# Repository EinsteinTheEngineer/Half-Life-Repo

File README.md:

# Half-Life-Repo

# WEEK 1

PURPOSE:
The purpose of my project is to create a simple yet extremely useful Flight computer, that can also be used for rockets, and this would simply send data, of temperature, bearing, and height, I can also create a velocity time graph with velocity put on the graph, and then simple derivate that to get acceleration, or I can just use the accelerometer, the MPU, and use that to give me a A vs. T graph. Why it exists: The reason is that flight computer is expensive and this is a fully done PCB, instead of me having to use a breadboard and have to worry about a loose connection, I can asssure myself that the copper traces will work. I love building plane and rockets, but what I like more is seeing them work and not fail, for this I need data! So I created this board to collect me data and so if it does fail, why and how can I prevent it the next time.

My project is a flight computer that will have multiple sensors talk to and esp32 wroom chip that will write the data to an SD card that will store it. The board consists of the following: ESP32-WROOM chip, MPU6050, BMP280, and an SD card logger. This was my plan at first, and it was changed a lot though. I add a DC to DC Buck converter it would convert 6v dc to 3.3v dc for the esp to then spit out 3.3v logic.
Started as this:

Then added the extra components:

Wired ground and live:

Wired the MPU: 

Wired the BMP:

Wired the SD card:

Finalized Schematic:

After fighting the ERC test

Then routed the board:

The 3d View

And finally done!

Here is My BOM for the parts I am using:

Designator	Category	Part / Value	Qty	Package / Footprint	Est. Unit Price (USD)	Est. Line Total (USD)	Distributor Link
U1	IC / Module	Espressif ESP32-WROOM-32E (or 32U)	1	ESP32-WROOM-32	7.21	7.21	digikey.com
U2	Sensor	Bosch BMP280	1	LGA-8 (2.0x2.5mm)	3	3	digikey.com
U3	Sensor	TDK InvenSense MPU-6050	1	QFN-24 (4x4mm)	4.25	4.25	digikey.com
U4	Power IC	Diodes Inc. AP63203WU-7	1	TSOT-23-6	0.65	0.65	digikey.com
U5	Interface IC	WCH CH340C	1	SOP-16	0.9	0.9	lcsc.com
J1	Connector	MicroSD Card Slot (Push-Push)	1	MicroSD_Card_Det	1.1	1.1	digikey.com
J2	Connector	2-Pin JST-PH 2.0mm Header	1	JST_PH_B2B-PH-K	0.25	0.25	digikey.com
J3	Connector	HRO TYPE-C-31-M-12 (16-Pin USB-C)	1	USB_C_Receptacle_16P	0.55	0.55	lcsc.com
SW1	Switch	SPDT SMD Slide Switch	1	SW_SPDT_PCM12	0.4	0.4	digikey.com
Q1, Q2	Transistor	S8050 (or MMBT3904) NPN	2	SOT-23	0.1	0.2	digikey.com
D1, D2	Diode	B5819W Schottky Diode	2	SOD-123	0.15	0.3	digikey.com
R1, R2	Resistor	5.1 kΩ (1%)	2	0603 (1608 Metric)	0.1	0.2	digikey.com
R3, R4, R_EN, R_IO0, R_SD1–3	Resistor	10 kΩ (1%)	7	0603 (1608 Metric)	0.1	0.7	digikey.com
R_TX	Resistor	1 kΩ (1%)	1	0603 (1608 Metric)	0.1	0.1	digikey.com
R_SDA, R_SCL	Resistor	4.7 kΩ (1%)	2	0603 (1608 Metric)	0.1	0.2	digikey.com
C5	Capacitor	2.2 nF (50V X7R)	1	0603 (1608 Metric)	0.1	0.1	digikey.com
C1–C4, C_DEC1–5	Capacitor	100 nF (16V/25V X7R)	7	0603 (1608 Metric)	0.1	0.7	digikey.com
C_EN	Capacitor	1 µF (16V X7R)	1	0603 (1608 Metric)	0.1	0.1	digikey.com
C_IN, C_BULK1–2	Capacitor	10 µF (25V X5R/X7R)	3	0805 (2012 Metric)	0.15	0.45	digikey.com
C6	Capacitor	22 µF (16V X5R/X7R)	1	0805 (2012 Metric)	0.2	0.2	digikey.com
L1	Inductor	3.3 µH (≥1.5A Shielded)	1	1210 (3225 Metric)	0.45	0.45	digikey.com

# WEEK 2

The purpose of this project is the create an enclosure for my PCB that I designed in week 1, this will make sure it isn't just sitting in there just chilling, I made sure to add mounting holes, and vents to make sure it will sit there and that it will have some breathability, and so it can cool, with the use of a fan two, since it will also use its antenna to communicate with my computer that's on the ground. So that means I technically have two ways to get data, from the SD card and from communication with my computer. I would trust the SD card more since the computer may have lost packets on the way and it could not be as reliable as a SD card, but it there as another way to have data.

Me personally, I printed this with PLA, since its cheap, light weight, and it's not like there's going to be such high temperatures, hence there is also a fan there for a reason.
PLA, print with 10-15% infill, you'll probably need support material, I have a K1C so no multi-material, so I just printed PLA supports.

# WEEK 3

This week I decided to create a recorder, it records sounds and stuff like that. The purpose for why I wanted to do this was because it was relatively simple, plus I learned about this new board the ESP32-S3-Zero, it's so good. It so useful, though its small it does a lot of things whilst being small. I was the perfect addition to the board, and just the same simple way of coding it. At first, I was about to use the actual esp32, which was most definitely going to be overkill for this simple guy. This board is a breakout board kind of, since it doesn't have an on-board ESP but the board will be put onto the thing.

Fully routed Schematic

With the cut outs

3D view

Here's the BOM

"Reference","Qty","Value","DNP","Exclude from BOM","Exclude from Board","Footprint","Datasheet"
"C1","1","100","","","","Capacitor_SMD:C_0805_2012Metric","~"
"C2","1","10000","","","","Capacitor_SMD:C_0805_2012Metric","~"
"C3","1","C","","","","Capacitor_SMD:C_0805_2012Metric","~"
"D1","1","LED","","","","LED_THT:LED_D3.0mm","~"
"J1,J2","2","Conn_01x09_Pin","","","","Connector_PinSocket_2.54mm:PinSocket_1x09_P2.54mm_Vertical","~"
"J3","1","Conn_01x06_Pin","","","","Connector_PinSocket_2.54mm:PinSocket_1x06_P2.54mm_Vertical","~"
"J4","1","Micro_SD_Card","","","","Connector_Card:microSD_HC_Wuerth_693072010801","https://www.we-online.com/components/products/datasheet/693072010801.pdf"
"J5","1","Screw_Terminal_01x02","","","","TerminalBlock_Phoenix:TerminalBlock_Phoenix_MKDS-1,5-2-5.08_1x02_P5.08mm_Horizontal","~"
"R1","1","330","","","","Resistor_SMD:R_0805_2012Metric","~"
"SW1","1","SW_Push","","","","Button_Switch_THT:SW_PUSH_6mm","~"

# WEEK 4

This week I focused on a weather and display thing. This was a simple yet easy idea that I would like to keep on my desk. It will show date, time, weather, and just a sleek design. The purpose of this was to create something very useful, and it will be simple enough to be easy to do.

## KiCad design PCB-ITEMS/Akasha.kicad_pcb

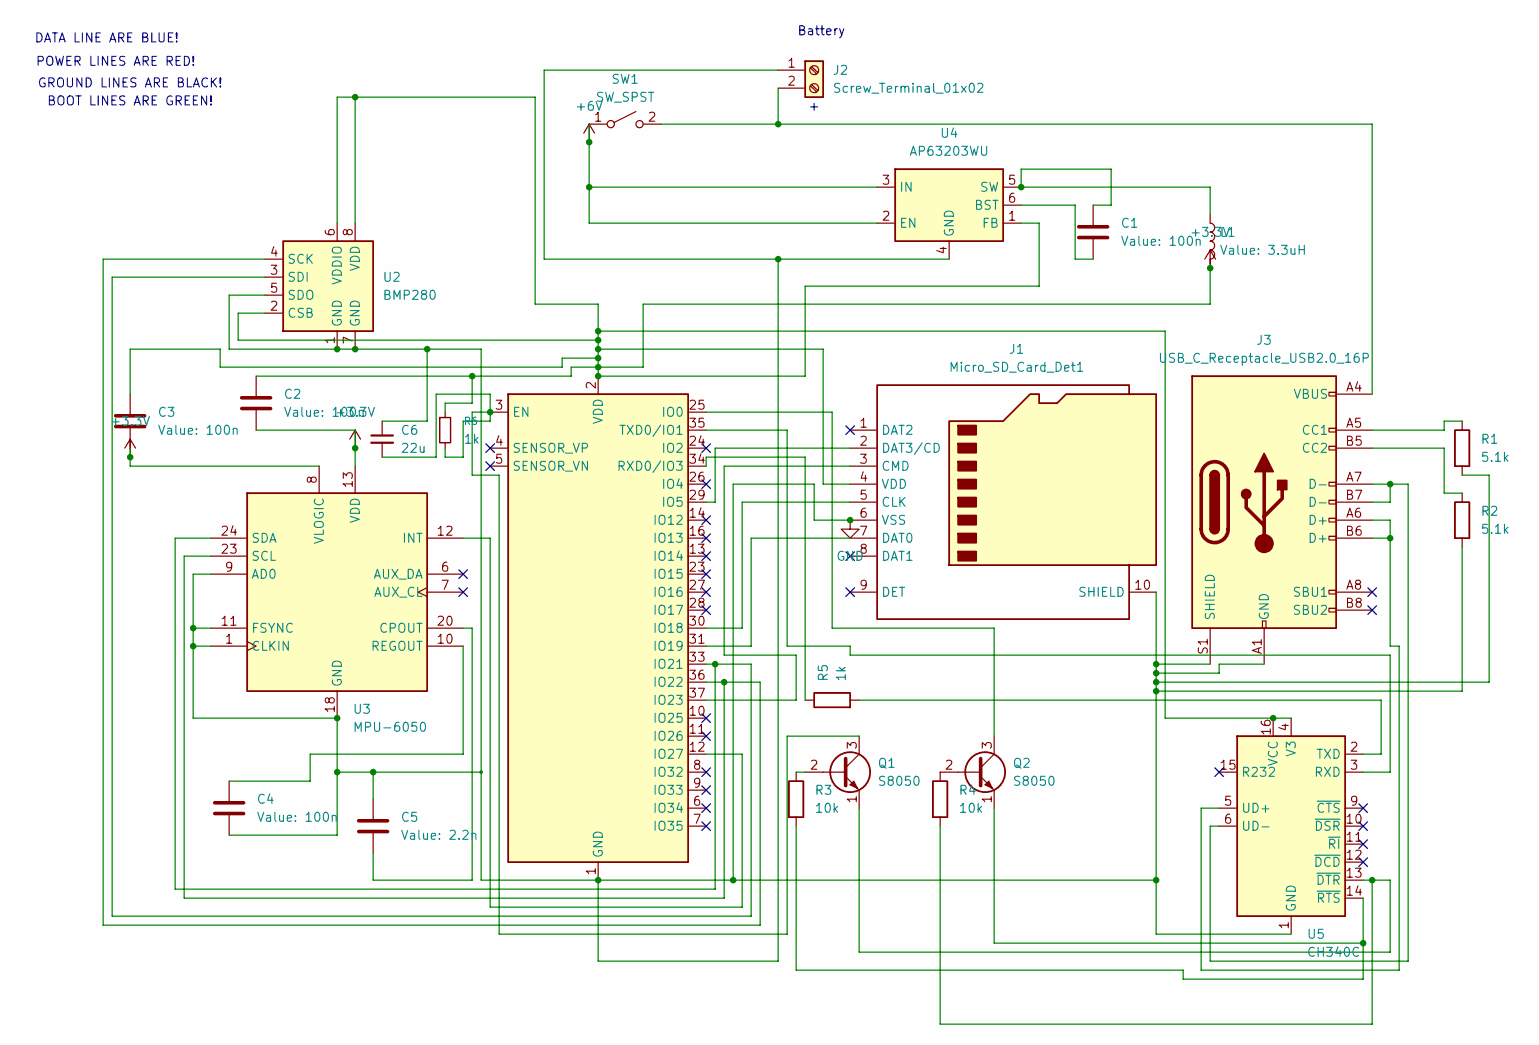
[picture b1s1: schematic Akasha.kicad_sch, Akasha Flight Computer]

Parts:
C1, C2, C3, C4: 100n; C_0603_1608Metric
C5: 2.2n; C_0603_1608Metric
C6: 22u; C_0805_2012Metric
J1: Micro_SD_Card_Det1; microSD_HC_Hirose_DM3AT-SF-PEJM5
J2: Screw_Terminal_01x02; TerminalBlock_Phoenix_MKDS-1,5-2-5.08_1x02_P5.08mm_Horizont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
J3: USB_C_Receptacle_USB2.0_16P; USB_C_Receptacle_HRO_TYPE-C-31-M-12
L1: 3.3uH; L_1210_3225Metric
Q1, Q2: S8050; SOT-23
R1, R2: 5.1k; R_0603_1608Metric
R3, R4: 10k; R_0603_1608Metric
R5, R6: 1k; R_0603_1608Metric
SW1: SW_SPST; SW_DIP_SPSTx01_Slide_6.7x4.1mm_W7.62mm_P2.54mm_LowProfile
U1: ESP32-WROOM-32E; ESP32-WROOM-32D
U2: BMP280; Bosch_LGA-8_2x2.5mm_P0.65mm_ClockwisePinNumbering
U3: MPU-6050; InvenSense_QFN-24_4x4mm_P0.5mm
U4: AP63203WU; TSOT-23-6
U5: CH340C; SOIC-16_3.9x9.9mm_P1.27mm

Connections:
+3.3V: C2.1, C2.2, C3.1, C3.2, J1.4 (VDD), L1.2, R6.1, U1.2 (VDD), U2.2 (CSB), U2.6 (VDDIO), U2.8 (VDD), U3.8 (VLOGIC), U3.13 (VDD), U4.1 (FB), U5.4 (V3), U5.16 (VCC)
+6V: SW1.1 (A), U4.2 (EN), U4.3 (IN)
GND: C4.2, C5.1, C6.1, J1.6 (VSS), J1.10 (SHIELD), J2.1, J3.A1 (GND), J3.A12 (GND), J3.B1 (GND), J3.B12 (GND), J3.S1 (SHIELD), R1.2, R2.2, U1.1 (GND), U1.15 (GND), U1.38 (GND), U1.39 (GND), U2.1 (GND), U2.5 (SDO), U2.7 (GND), U3.1 (CLKIN), U3.9 (AD0), U3.11 (FSYNC), U3.18 (GND), U4.4 (GND), U5.1 (GND)
unnamed: J1.5 (CLK), U1.30 (IO18)
unnamed: J1.3 (CMD), U1.37 (IO23)
unnamed: J1.7 (DAT0), U1.31 (IO19)
unnamed: J1.2 (DAT3/CD), U1.29 (IO5)
unnamed: J2.2, J3.A4 (VBUS), J3.A9 (VBUS), J3.B4 (VBUS), J3.B9 (VBUS), SW1.2 (B)
unnamed: J3.A5 (CC1), R1.1
unnamed: J3.B5 (CC2), R2.1
unnamed: Q1.2 (B), R3.1
unnamed: C6.2, Q1.3 (C), R6.2, U1.3 (EN)
unnamed: Q1.1 (E), R4.2, U5.13 (~DTR)
unnamed: Q2.2 (B), R4.1
unnamed: Q2.3 (C), U1.25 (IO0)
unnamed: Q2.1 (E), R3.2, U5.14 (~RTS)
unnamed: U1.33 (IO21), U2.3 (SDI), U3.24 (SDA)
unnamed: U1.36 (IO22), U2.4 (SCK), U3.23 (SCL)
unnamed: U1.12 (IO27), U3.12 (INT)
unnamed: R5.1, U1.34 (RXD0/IO3)
unnamed: U1.35 (TXD0/IO1), U5.3 (RXD)
unnamed: C5.2, U3.20 (CPOUT)
unnamed: C4.1, U3.10 (REGOUT)
unnamed: C1.2, U4.6 (BST)
unnamed: C1.1, L1.1, U4.5 (SW)
unnamed: R5.2, U5.2 (TXD)
unnamed: J3.A6 (D+), J3.B6 (D+), U5.5 (UD+)
unnamed: J3.A7 (D-), J3.B7 (D-), U5.6 (UD-)

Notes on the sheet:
POWER LINES ARE RED!
Battery
BOOT LINES ARE GREEN!
DATA LINE ARE BLUE!
GROUND LINES ARE BLACK!

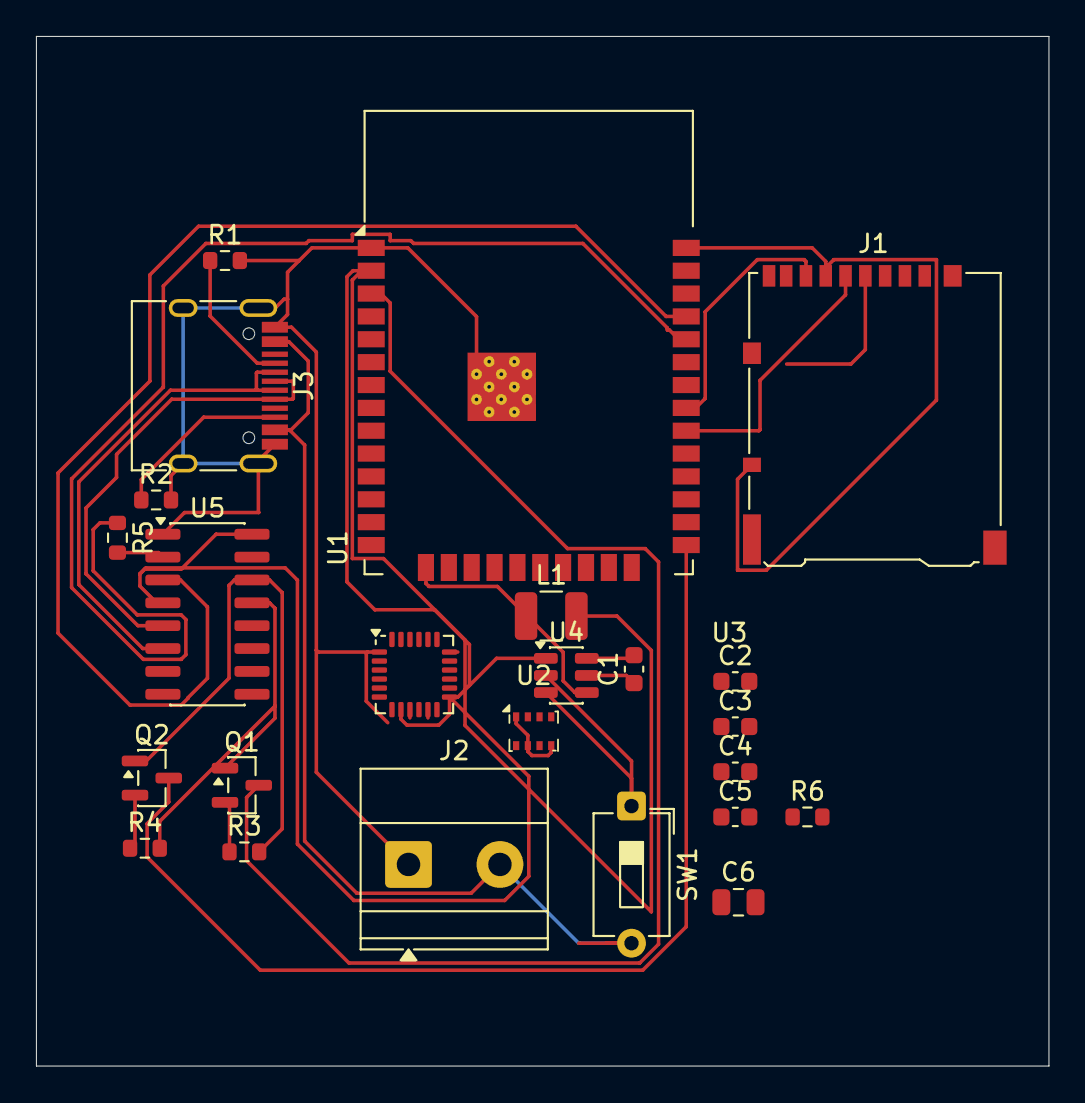
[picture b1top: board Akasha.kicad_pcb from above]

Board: 2 copper layers, 56.2 x 57.2 mm, 24 parts (0 on the bottom side), 28 nets.

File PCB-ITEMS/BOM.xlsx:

Designator | Category | Part / Value | Qty | Package / Footprint | Est. Unit Price (USD) | Est. Line Total (USD) | Distributor Link
U1 | IC / Module | Espressif ESP32-WROOM-32E (or 32U) | 1.0 | ESP32-WROOM-32 | 7.21 | 7.21 | digikey.com
U2 | Sensor | Bosch BMP280 | 1.0 | LGA-8 (2.0x2.5mm) | 3.0 | 3.0 | digikey.com
U3 | Sensor | TDK InvenSense MPU-6050 | 1.0 | QFN-24 (4x4mm) | 4.25 | 4.25 | digikey.com
U4 | Power IC | Diodes Inc. AP63203WU-7 | 1.0 | TSOT-23-6 | 0.65 | 0.65 | digikey.com
U5 | Interface IC | WCH CH340C | 1.0 | SOP-16 | 0.9 | 0.9 | lcsc.com
J1 | Connector | MicroSD Card Slot (Push-Push) | 1.0 | MicroSD_Card_Det | 1.1 | 1.1 | digikey.com
J2 | Connector | 2-Pin JST-PH 2.0mm Header | 1.0 | JST_PH_B2B-PH-K | 0.25 | 0.25 | digikey.com
J3 | Connector | HRO TYPE-C-31-M-12 (16-Pin USB-C) | 1.0 | USB_C_Receptacle_16P | 0.55 | 0.55 | lcsc.com
SW1 | Switch | SPDT SMD Slide Switch | 1.0 | SW_SPDT_PCM12 | 0.4 | 0.4 | digikey.com
Q1, Q2 | Transistor | S8050 (or MMBT3904) NPN | 2.0 | SOT-23 | 0.1 | 0.2 | digikey.com
D1, D2 | Diode | B5819W Schottky Diode | 2.0 | SOD-123 | 0.15 | 0.3 | digikey.com
R1, R2 | Resistor | 5.1 kΩ (1%) | 2.0 | 0603 (1608 Metric) | 0.1 | 0.2 | digikey.com
R3, R4, R_EN, R_IO0, R_SD1–3 | Resistor | 10 kΩ (1%) | 7.0 | 0603 (1608 Metric) | 0.1 | 0.7 | digikey.com
R_TX | Resistor | 1 kΩ (1%) | 1.0 | 0603 (1608 Metric) | 0.1 | 0.1 | digikey.com
R_SDA, R_SCL | Resistor | 4.7 kΩ (1%) | 2.0 | 0603 (1608 Metric) | 0.1 | 0.2 | digikey.com
C5 | Capacitor | 2.2 nF (50V X7R) | 1.0 | 0603 (1608 Metric) | 0.1 | 0.1 | digikey.com
C1–C4, C_DEC1–5 | Capacitor | 100 nF (16V/25V X7R) | 7.0 | 0603 (1608 Metric) | 0.1 | 0.7 | digikey.com
C_EN | Capacitor | 1 µF (16V X7R) | 1.0 | 0603 (1608 Metric) | 0.1 | 0.1 | digikey.com
C_IN, C_BULK1–2 | Capacitor | 10 µF (25V X5R/X7R) | 3.0 | 0805 (2012 Metric) | 0.15 | 0.45 | digikey.com
C6 | Capacitor | 22 µF (16V X5R/X7R) | 1.0 | 0805 (2012 Metric) | 0.2 | 0.2 | digikey.com
L1 | Inductor | 3.3 µH (≥1.5A Shielded) | 1.0 | 1210 (3225 Metric) | 0.45 | 0.45 | digikey.com

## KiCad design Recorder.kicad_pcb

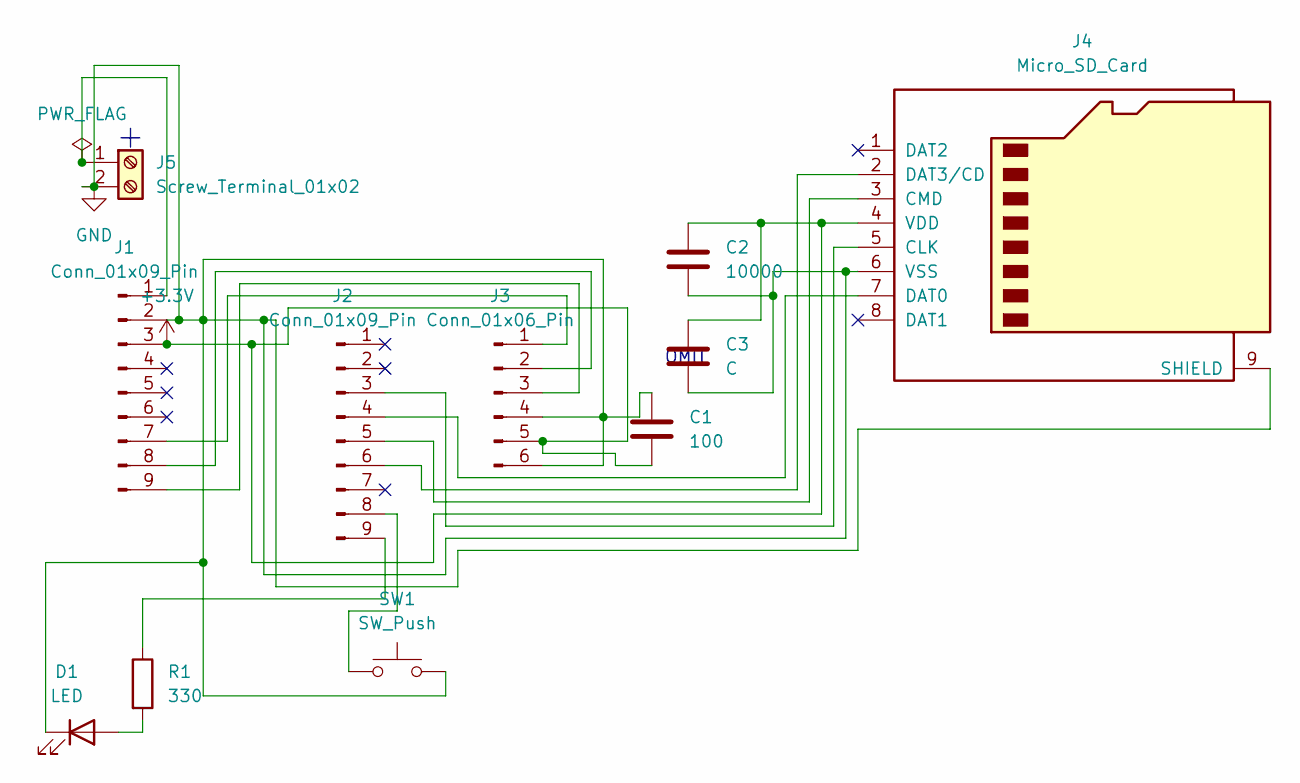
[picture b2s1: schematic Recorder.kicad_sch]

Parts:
C1: 100; C_0805_2012Metric
C2: 10000; C_0805_2012Metric
C3: C; C_0805_2012Metric
D1: LED; LED_D3.0mm
J1, J2: Conn_01x09_Pin; PinSocket_1x09_P2.54mm_Vertical
J3: Conn_01x06_Pin; PinSocket_1x06_P2.54mm_Vertical
J4: Micro_SD_Card; microSD_HC_Wuerth_693072010801
J5: Screw_Terminal_01x02; TerminalBlock_Phoenix_MKDS-1,5-2-5.08_1x02_P5.08mm_Horizont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
R1: 330; R_0805_2012Metric
SW1: SW_Push; SW_PUSH_6mm

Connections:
+3.3V: C1.2, C2.1, C3.1, J1.3, J3.5, J4.4 (VDD)
GND: C1.1, C2.2, C3.2, D1.1 (K), J1.2, J3.4, J3.6, J4.6 (VSS), J4.9 (SHIELD), J5.2, SW1.2
unnamed: D1.2 (A), R1.2
unnamed: J1.1, J5.1
unnamed: J1.7, J3.1
unnamed: J1.8, J3.2
unnamed: J1.9, J3.3
unnamed: J2.3, J4.5 (CLK)
unnamed: J2.4, J4.7 (DAT0)
unnamed: J2.5, J4.3 (CMD)
unnamed: J2.6, J4.2 (DAT3/CD)
unnamed: J2.8, SW1.1
unnamed: J2.9, R1.1

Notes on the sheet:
OMIT

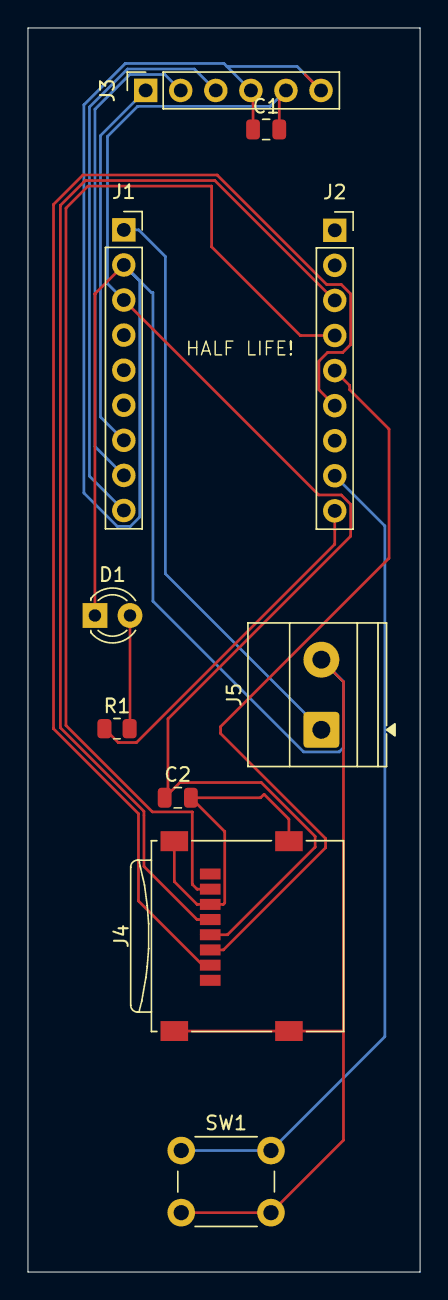
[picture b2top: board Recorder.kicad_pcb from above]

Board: 2 copper layers, 28.4 x 90.1 mm, 10 parts (0 on the bottom side), 13 nets.
